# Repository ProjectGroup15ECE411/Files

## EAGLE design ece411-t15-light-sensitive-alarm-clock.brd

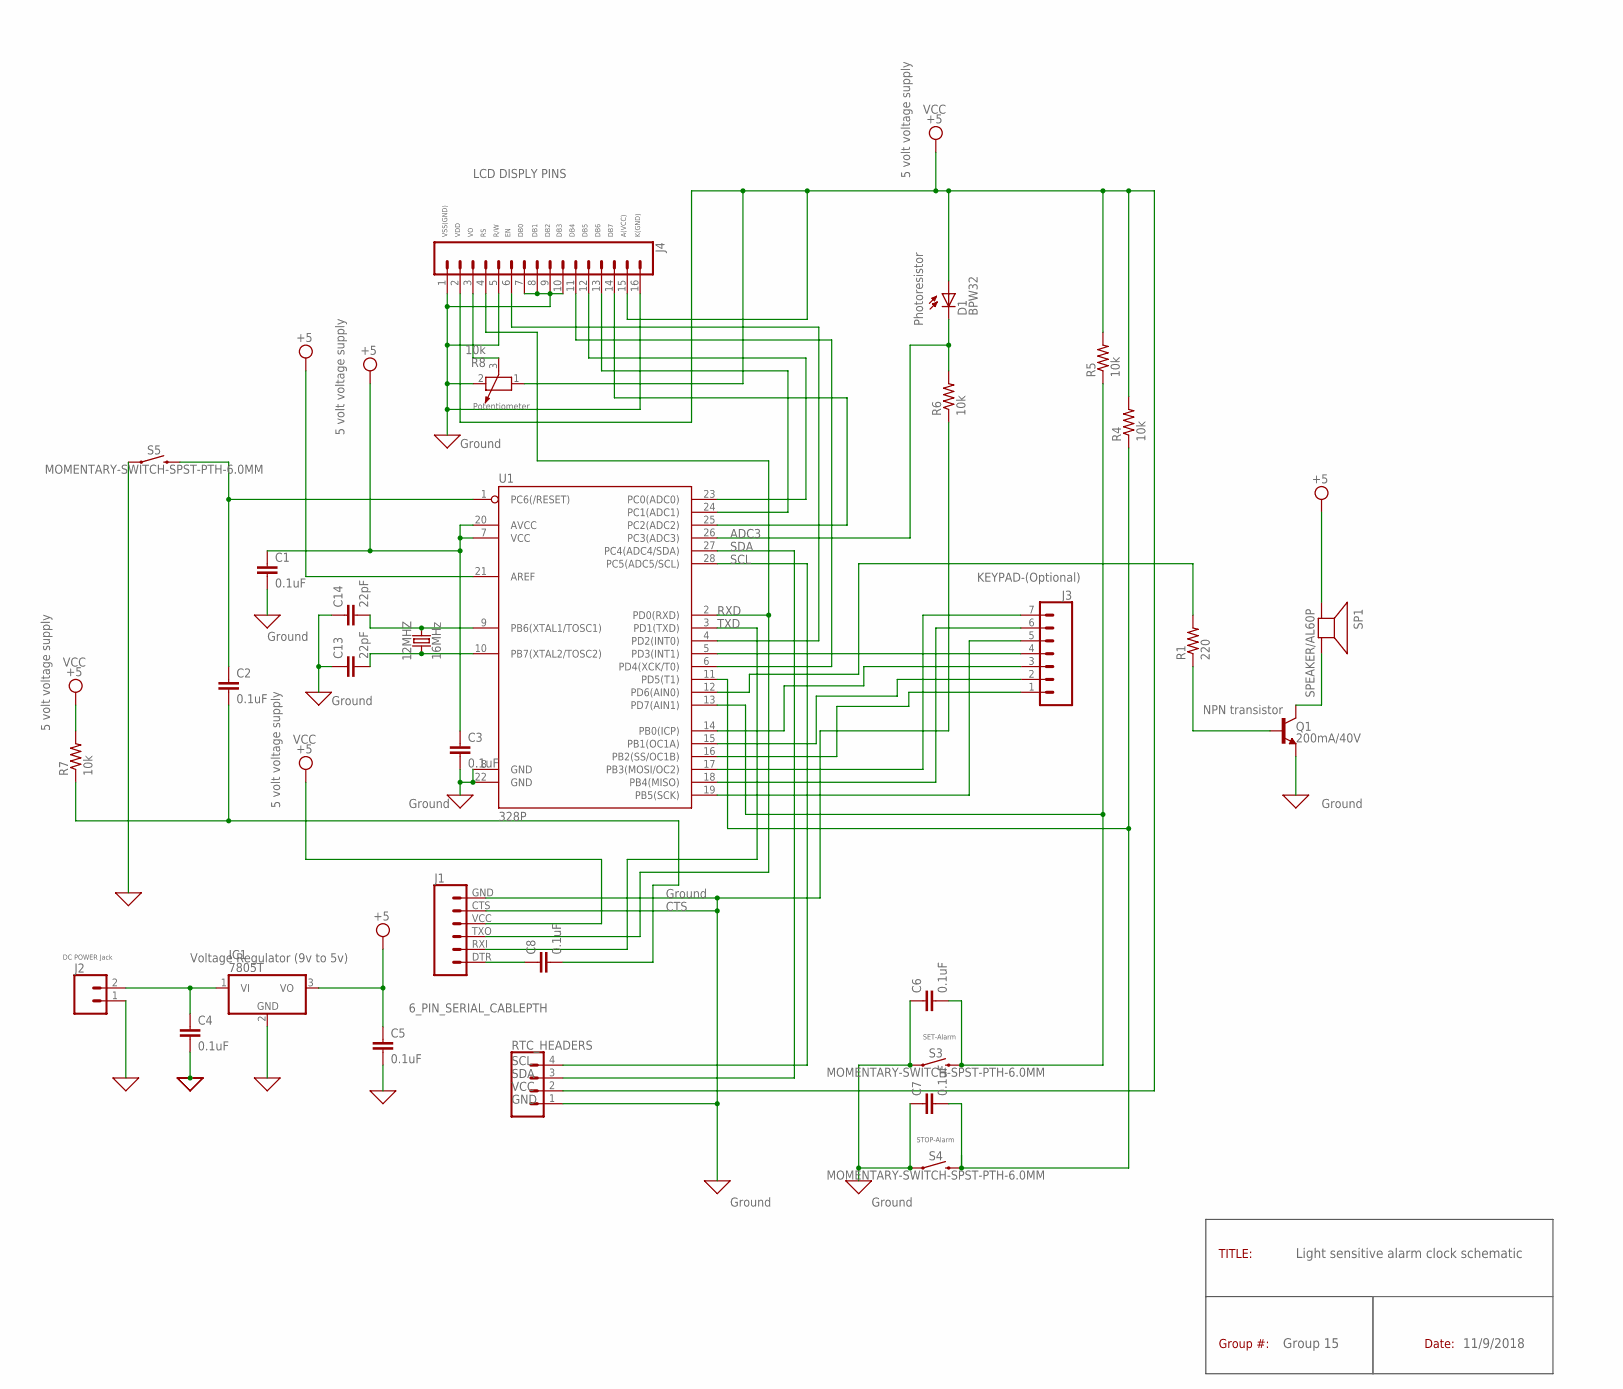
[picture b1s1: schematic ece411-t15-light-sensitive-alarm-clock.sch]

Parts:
12MHZ: 16MHz; CRYSTAL-PTH-2X6-CYL
C1, C2, C3, C4, C5, C6, C7, C8: 0.1uF; 0603
C13, C14: 22pF; 0603
D1: BPW32
IC1: 7805T; TO220H
J1: 6_PIN_SERIAL_CABLEPTH; FTDI_BASIC
J2: CONN_02; 1X02
J3: CONN_07; 1X07
J4: CONN_16; 1X16
Q1: 200mA/40V; TO-92
R1: 220; R0603
R4, R5, R6, R7: 10k; R0603
R8: 10k; PT-10
RTC_HEADERS: CONN_04; 1X04
S3, S4, S5: MOMENTARY-SWITCH-SPST-PTH-6.0MM; TACTILE_SWITCH_PTH_6.0MM
SP1: SPEAKER/AL60P; AL60P
U1: 328P; DIP28

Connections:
0: C1.2, C3.2, C4.2, C5.2, C6.1, C7.1, C13.1, C14.1, IC1.2 (GND), J1.CTS (5), J1.GND (6), J2.1, J4.1, J4.5, J4.7, J4.8, J4.9, J4.10, J4.16, Q1.1 (E), R6.1, R8.2, RTC_HEADERS.1, S3.1, S4.1, S5.1, U1.8 (GND), U1.22 (GND)
ADC0: C7.2, R4.1, S4.3 (2), U1.11 (PD5(T1))
ADC1: C6.2, R5.1, S3.3 (2), U1.13 (PD7(AIN1))
unnamed: 12MHZ.2, C14.2, U1.9 (PB6(XTAL1/TOSC1))
unnamed: 12MHZ.1, C13.2, U1.10 (PB7(XTAL2/TOSC2))
unnamed: Q1.3 (C), SP1.2 (-)
unnamed: Q1.2 (B), R1.1
unnamed: RTC_HEADERS.3, U1.27 (PC4(ADC4/SDA))
unnamed: C4.1, IC1.1 (VI), J2.2
unnamed: J1.RXI (2), U1.3 (PD1(TXD))
unnamed: RTC_HEADERS.4, U1.28 (PC5(ADC5/SCL))
unnamed: J1.TXO (3), J4.4, U1.2 (PD0(RXD))
unnamed: C8.1, J1.DTR (1)
unnamed: J4.3, R8.3
unnamed: J4.6, U1.4 (PD2(INT0))
unnamed: J3.4, U1.5 (PD3(INT1))
unnamed: R1.2, U1.12 (PD6(AIN0))
unnamed: J4.12, U1.23 (PC0(ADC0))
unnamed: J4.13, U1.24 (PC1(ADC1))
unnamed: D1.K (C), R6.2, U1.26 (PC3(ADC3))
unnamed: J4.14, U1.25 (PC2(ADC2))
unnamed: J3.3, U1.14 (PB0(ICP))
unnamed: C2.2, C8.2, R7.1
unnamed: J4.11, U1.6 (PD4(XCK/T0))
unnamed: J3.2, U1.15 (PB1(OC1A))
unnamed: J3.1, U1.16 (PB2(SS/OC1B))
unnamed: C2.1, S5.3 (2), U1.1 (PC6(/RESET))
unnamed: J3.7, U1.17 (PB3(MOSI/OC2))
unnamed: J3.6, U1.18 (PB4(MISO))
unnamed: J3.5, U1.19 (PB5(SCK))
VCC: C1.1, C3.1, C5.1, D1.A, IC1.3 (VO), J1.VCC (4), J4.2, J4.15, R4.2, R5.2, R7.2, R8.1, RTC_HEADERS.2, SP1.1 (+), U1.7 (VCC), U1.20 (AVCC), U1.21 (AREF)

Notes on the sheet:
5 volt voltage supply
LCD DISPLY PINS
Ground
Potentiometer
Light sensitive alarm clock schematic
Group 15
SCL
RXD
TXD
CTS
ADC3
SDA
TITLE:
Group #:
Date:
11/9/2018
VCC
Voltage Regulator (9v to 5v)
SET-Alarm
STOP-Alarm
Photoresistor
NPN transistor
GND
VSS(GND)
VDD
R/W
DB0
DB1
DB2
DB3
DB4
DB5
DB6
DB7
A(VCC)
K(GND)
DC POWER Jack
KEYPAD-(Optional)

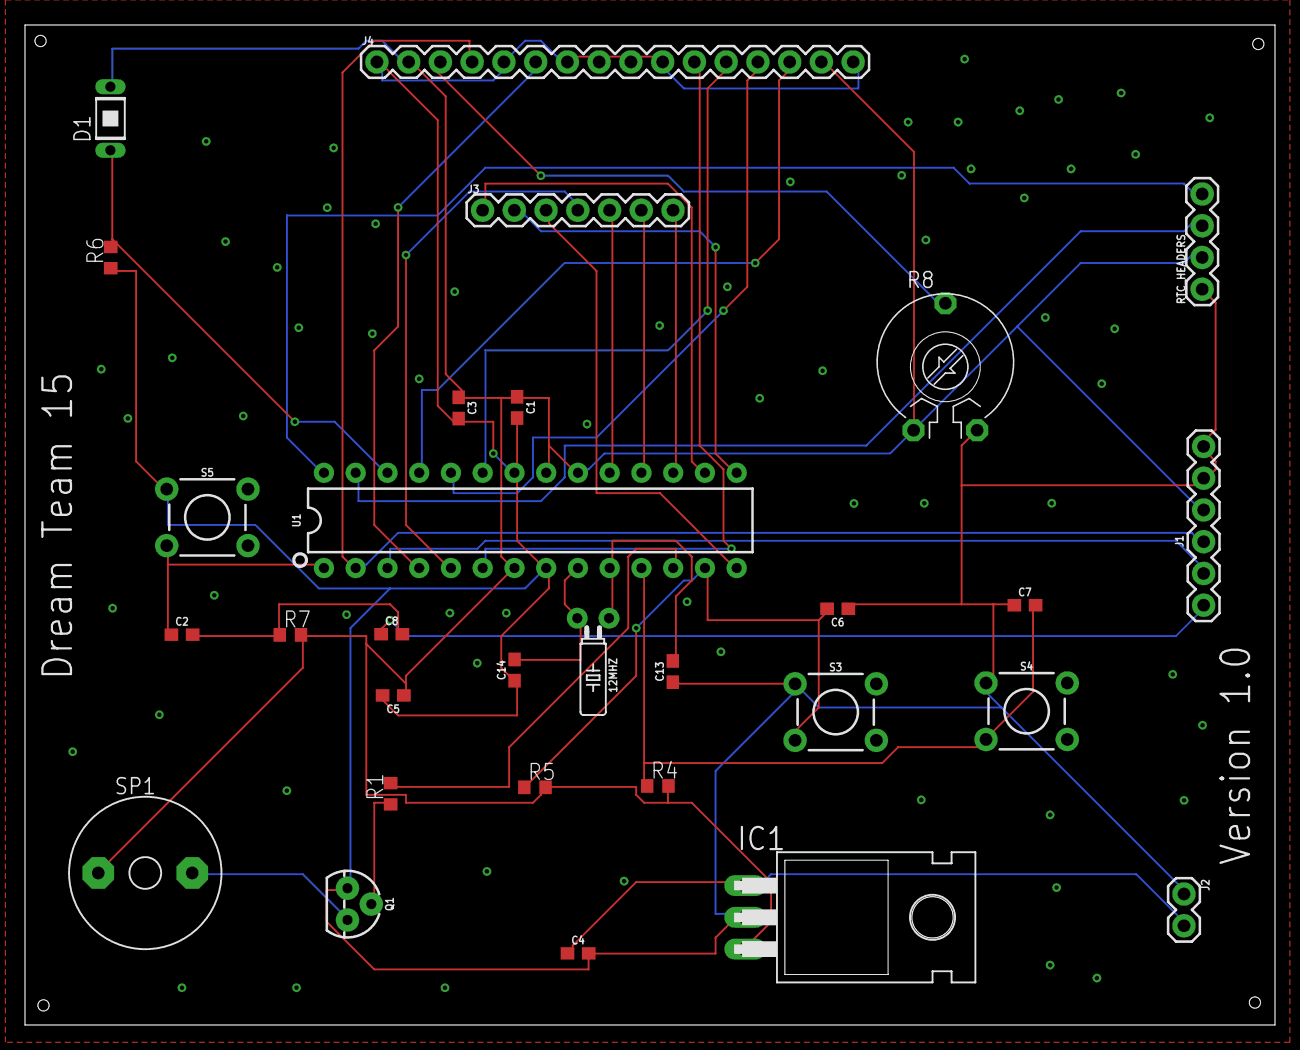
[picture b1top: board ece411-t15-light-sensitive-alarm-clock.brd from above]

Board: 2 copper layers, 100.0 x 80.0 mm, 30 parts (0 on the bottom side), 31 nets.

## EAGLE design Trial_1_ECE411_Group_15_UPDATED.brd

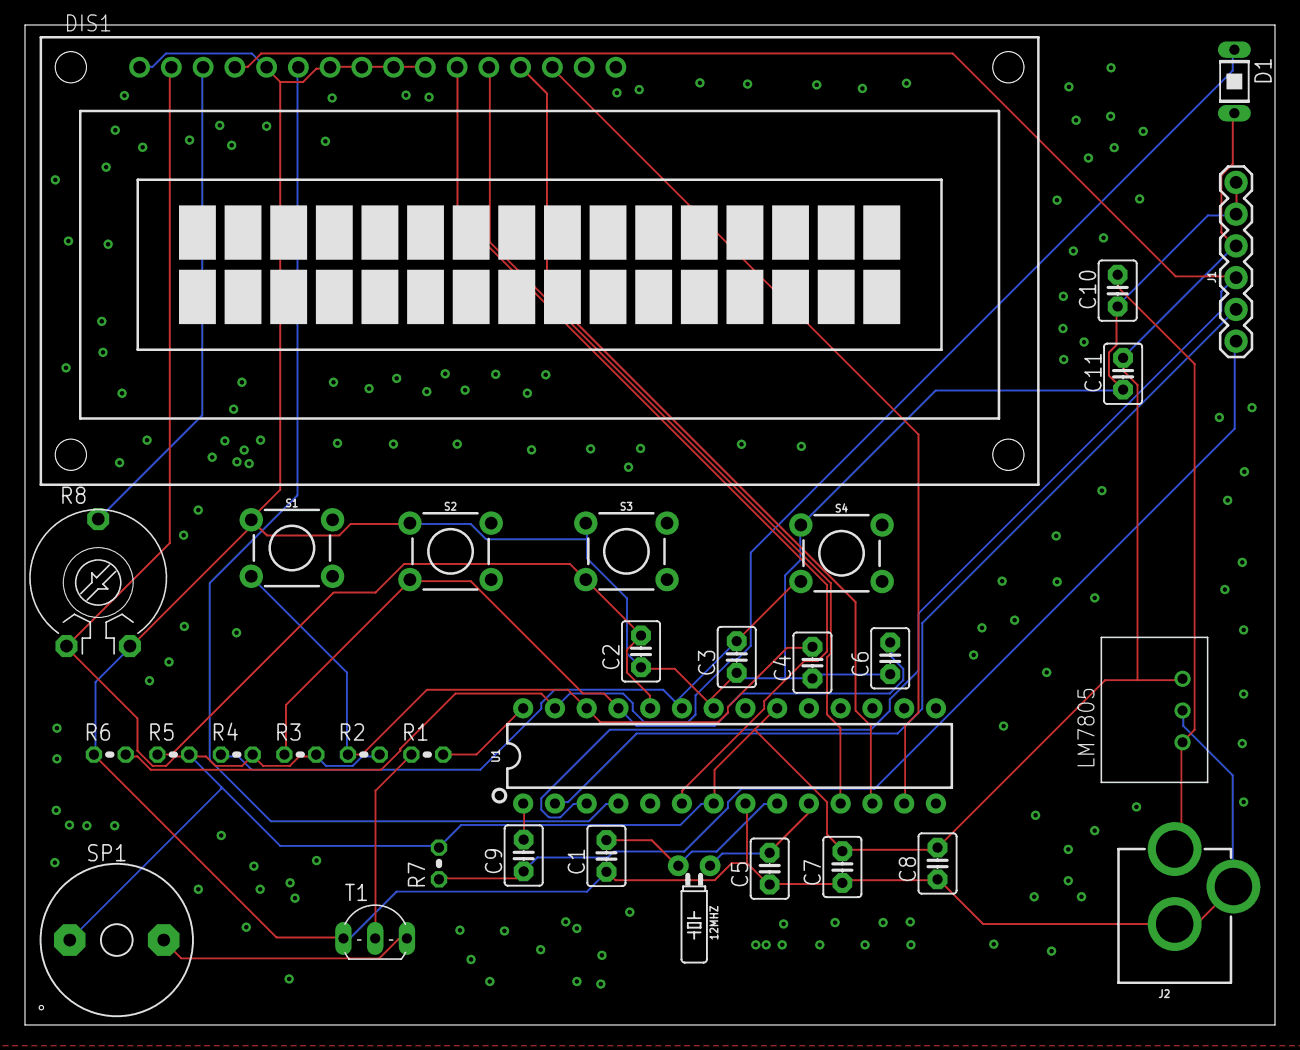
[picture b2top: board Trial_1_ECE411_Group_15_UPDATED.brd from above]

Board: 2 copper layers, 100.0 x 80.0 mm, 32 parts (0 on the bottom side), 23 nets.

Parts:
12MHZ: CRYSTAL-PTH-2X6-CYL
C1, C5: 18p; C2.5-3
C2, C3, C4, C6: 100n; C2.5-3
C7, C8, C9, C10, C11: 0.1u; C2.5-3
D1: BPW32
DIS1: TUXGR_16X2_R2
J1: 6_PIN_SERIAL_CABLEPTH; FTDI_BASIC
J2: POWER_JACK; POWER_JACK_PTH
LM7805: R-78E5.0-1.0; DC-DC_CONVERTER_78XX
R1: 220; 0204V
R2, R3, R4, R5, R7: 10k; 0204V
R6: 1k; 0204V
R8: 10k; PT-10
S1, S2, S3, S4: MOMENTARY-SWITCH-SPST-PTH-6.0MM; TACTILE_SWITCH_PTH_6.0MM
SP1: SPEAKER/AL60P; AL60P
T1: 2N2222; TO92-EBC-OVAL
U1: 328P; DIP28

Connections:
0: C1.1, C2.1, C3.1, C4.1, C5.1, C6.1, C7.1, C8.1, C10.1, C11.1, DIS1.1, DIS1.5, DIS1.7, DIS1.8, DIS1.9, DIS1.10, J1.CTS, J1.GND, J2.GND, J2.GNDBREAK, LM7805.GND, R6.1, R8.2, S1.1, S2.1, S3.1, S4.1, T1.E, U1.8, U1.22
ADC0: C3.2, R4.1, S4.3, U1.23
ADC1: C2.2, R5.1, S3.3, U1.24
ADC2: C6.2, R3.1, S2.3, U1.25
ADC3: C4.2, R2.1, S1.3, U1.26
unnamed: 12MHZ.2, C1.2, U1.9
unnamed: 12MHZ.1, C5.2, U1.10
unnamed: SP1.2, T1.C
unnamed: R1.1, T1.B
unnamed: C10.2, J2.PWR, LM7805.VIN
unnamed: J1.RXI, U1.2
unnamed: DIS1.4, J1.TXO, U1.3
unnamed: DIS1.3, R8.3
unnamed: DIS1.11, U1.6
unnamed: DIS1.12, U1.11
unnamed: DIS1.13, U1.12
unnamed: DIS1.14, U1.13
unnamed: D1.K, R6.2, U1.27
unnamed: R1.2, U1.28
unnamed: C9.1, J1.DTR, R7.1
unnamed: DIS1.6, U1.4
unnamed: C9.2, U1.1
VCC: C7.2, C8.2, C11.2, D1.A, DIS1.2, J1.VCC, LM7805.VOUT, R2.2, R3.2, R4.2, R5.2, R7.2, R8.1, SP1.1, U1.7, U1.20

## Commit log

2018-11-05 Add files via upload
    The Updated schematic, and the layout of the light sensitive alarm clock project.

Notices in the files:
parts and their libraries:
SparkFun-Connectors: Licensing: Creative Commons ShareAlike 4.0 International - https://creativecommons.org/licenses/by-sa/4.0
